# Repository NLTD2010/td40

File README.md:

# TD40

> **TD40** is a compact 40% mechanical keyboard designed for efficiency and portability.  
> It features **hot-swappable switches**, a **rotary knob**, an **OLED display**, **wireless connectivity**, and **per-key RGB lighting**.

---

## 🖼️ Preview

| TD40 (Back) | PCB |
|-------------|-----|
|  |  |

---

## ✨ Features
- Clean PCB design with **SMD soldering**
- **Nice!Nano v2** microcontroller – USB-C & Bluetooth compatible
- **Rotary encoder** + knob
- **0.91" OLED** screen
- **Per-key RGB** lighting
- **Hot-swappable** switches
- Open & visible components (Plaid / Romac style)
- Simple, flexible case options

---

## ⌨️ Layout

---

## 📦 Bill of Materials

| # | Item                         | Qty |
|---|------------------------------|----:|
| 1 | PCB                          | 1 |
| 2 | FR4 plate                    | 1 |
| 3 | Mica case                    | 1 |
| 4 | Controller (**Nice!Nano v2**) | 1 |
| 5 | Switches (5-pin MX footprint)| 45 |
| 6 | Kailh hotswap socket         | 45 |
| 7 | Diodes                       | 46 |
| 8 | Rotary encoder & knob        | 1 |
| 9 | 0.91" OLED screen            | 1 |

---

💡 **Tip:** Check out the [repository](https://github.com/NLTD2010/td40) for firmware, build guide, and more!

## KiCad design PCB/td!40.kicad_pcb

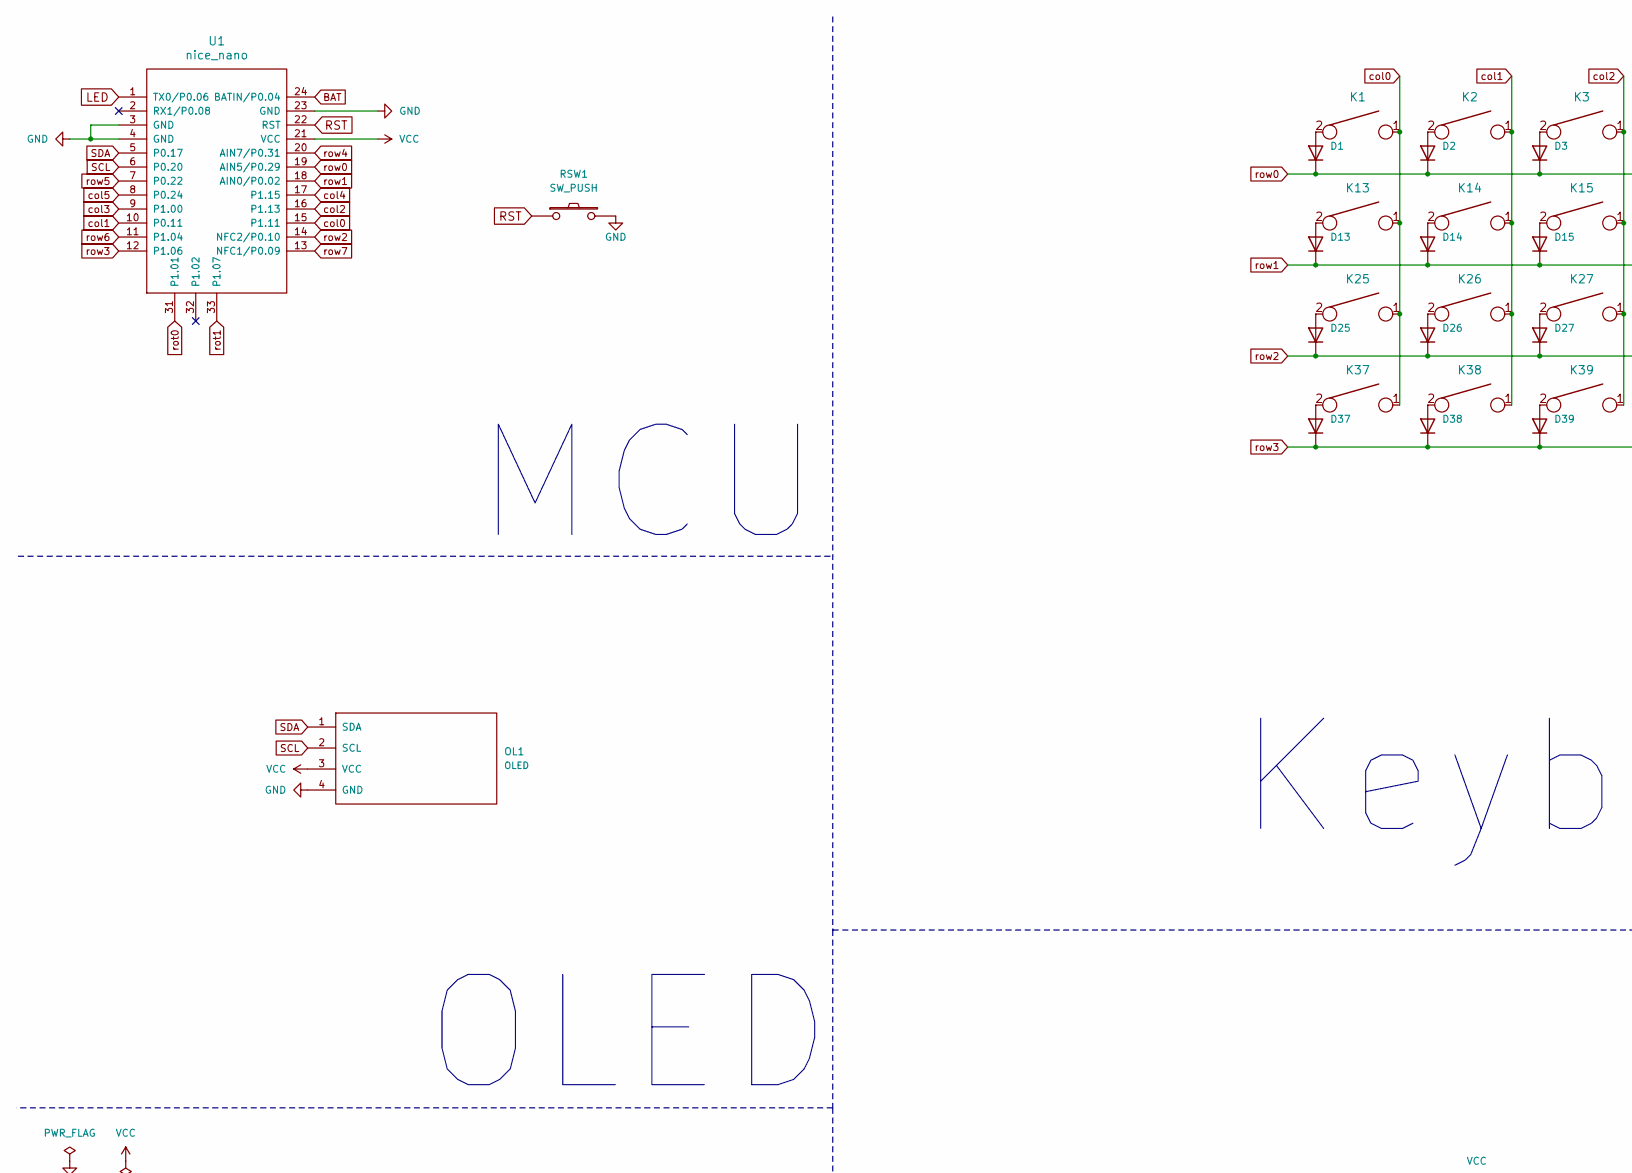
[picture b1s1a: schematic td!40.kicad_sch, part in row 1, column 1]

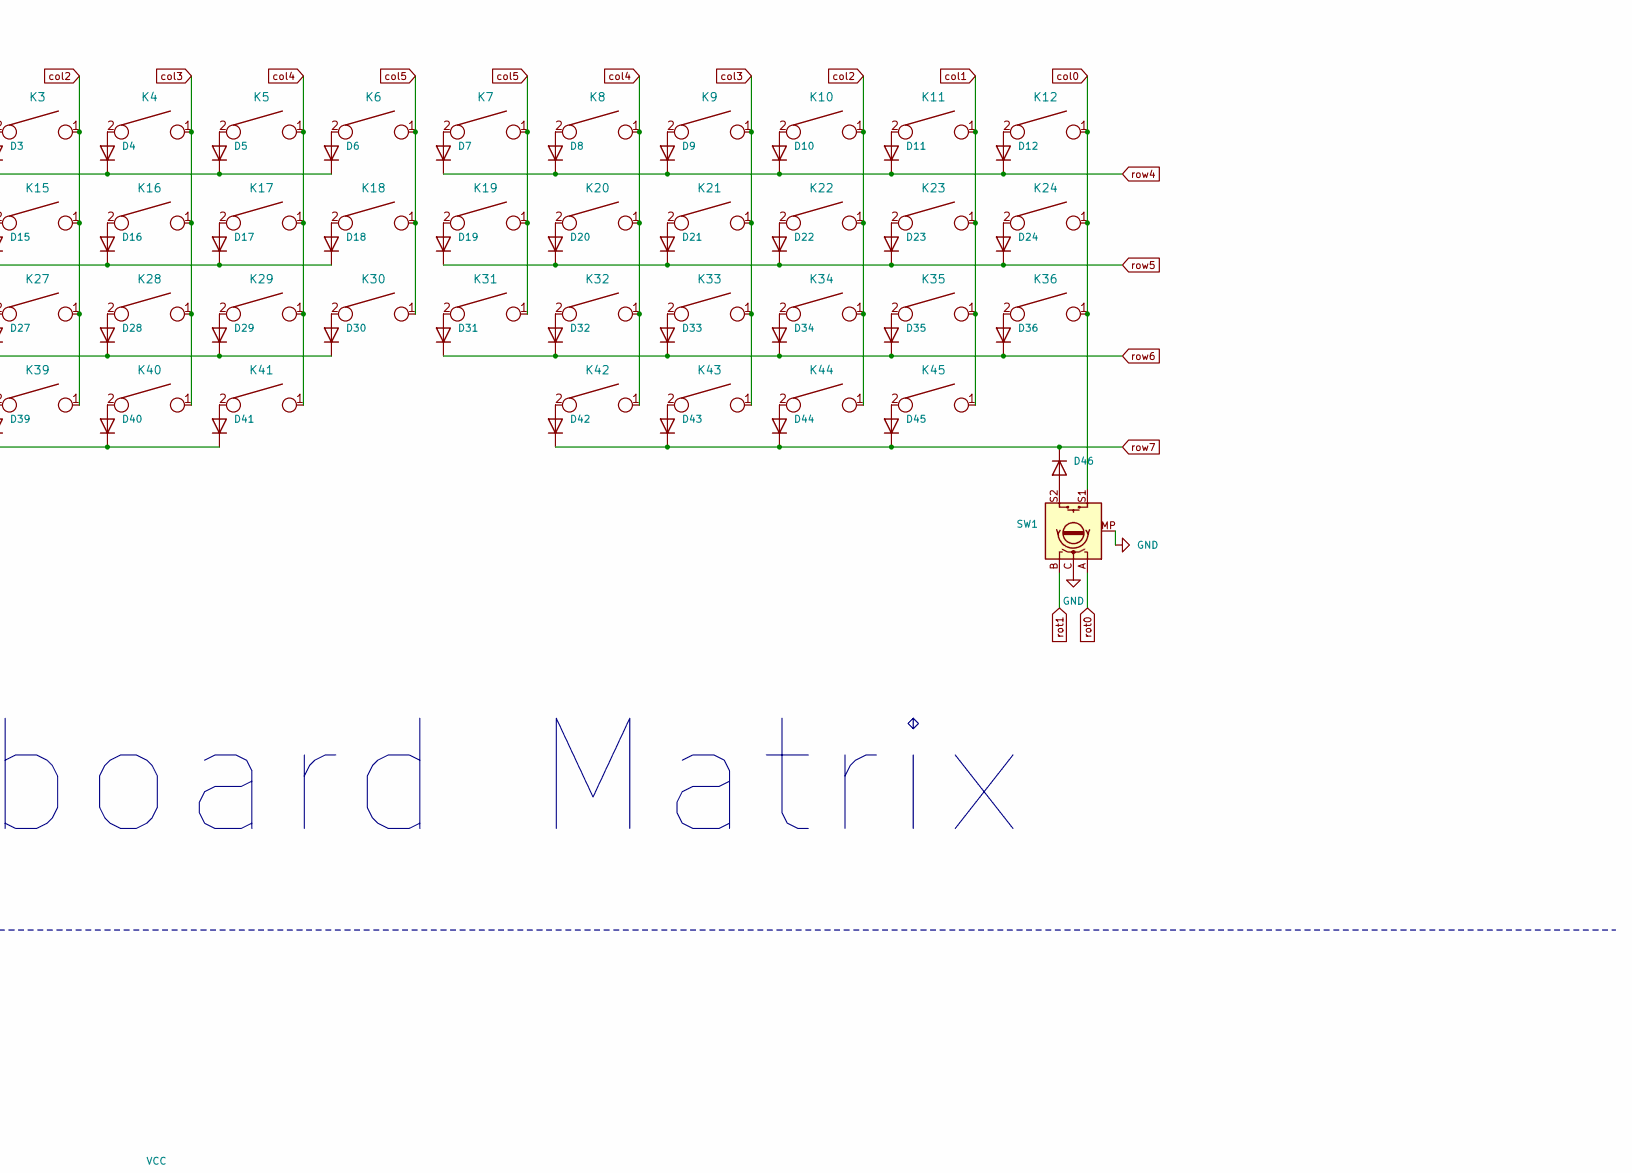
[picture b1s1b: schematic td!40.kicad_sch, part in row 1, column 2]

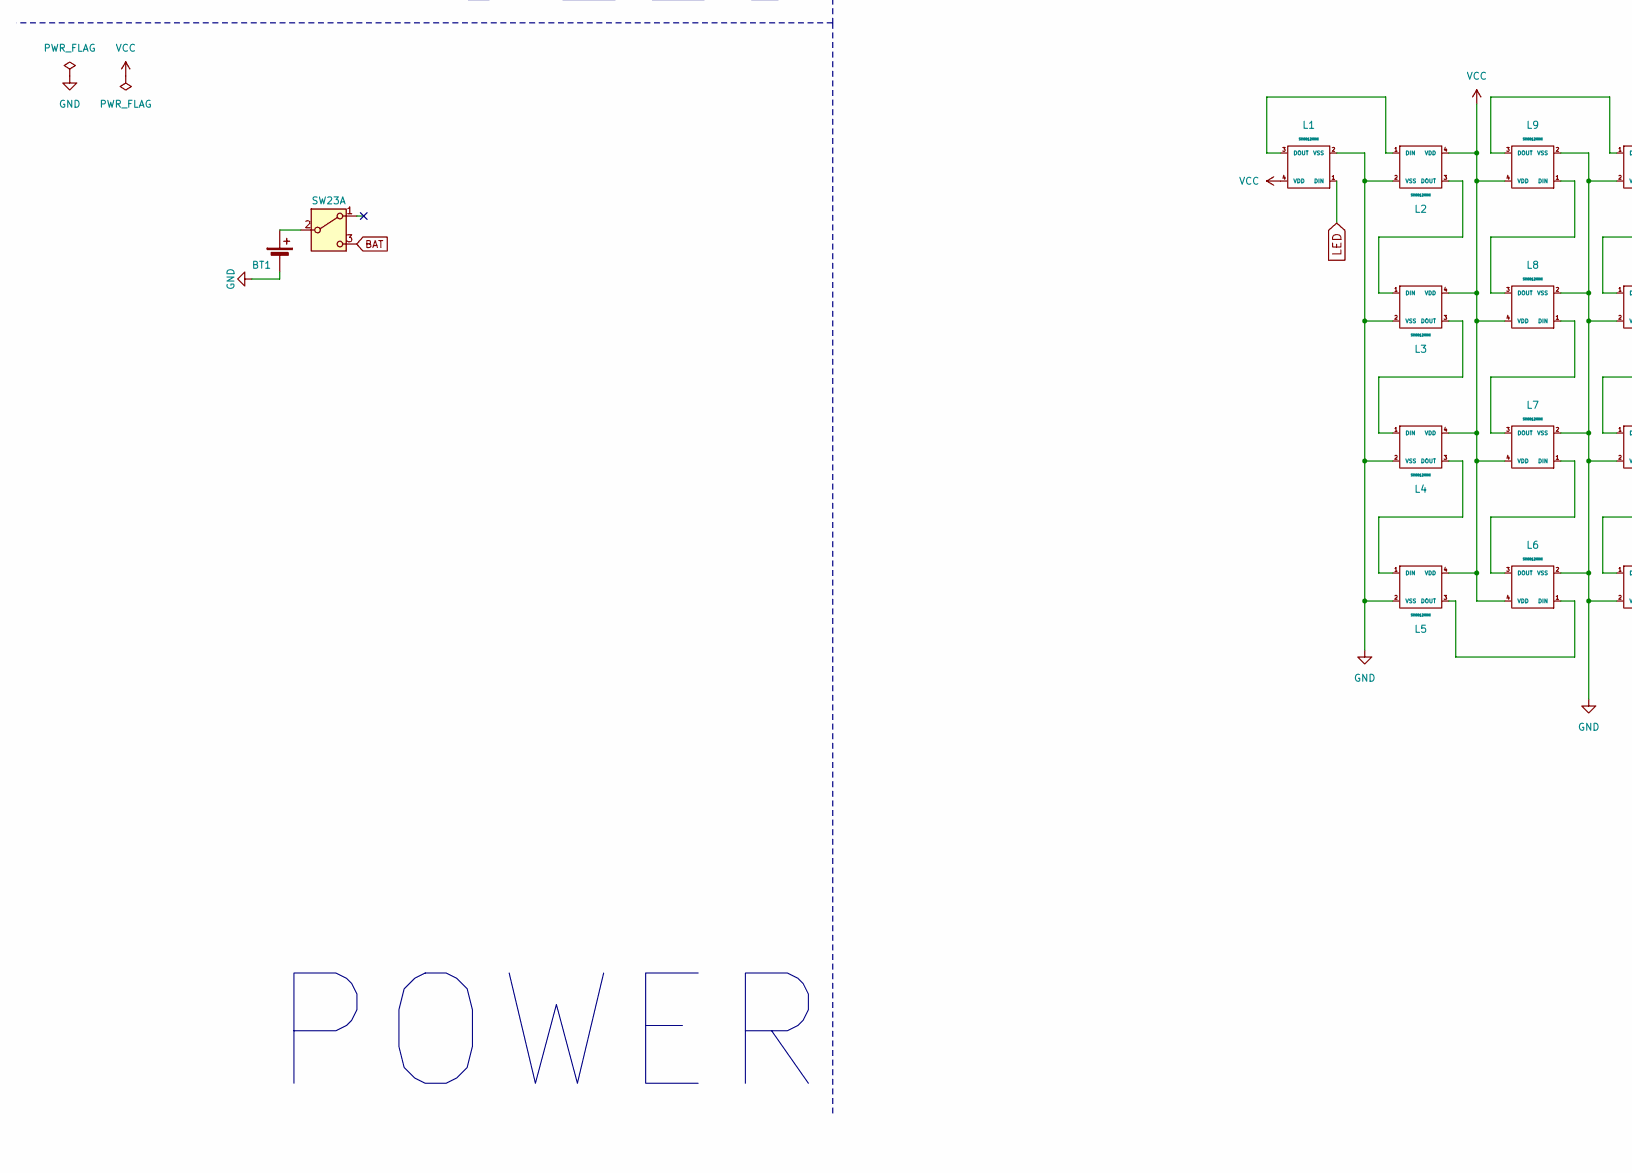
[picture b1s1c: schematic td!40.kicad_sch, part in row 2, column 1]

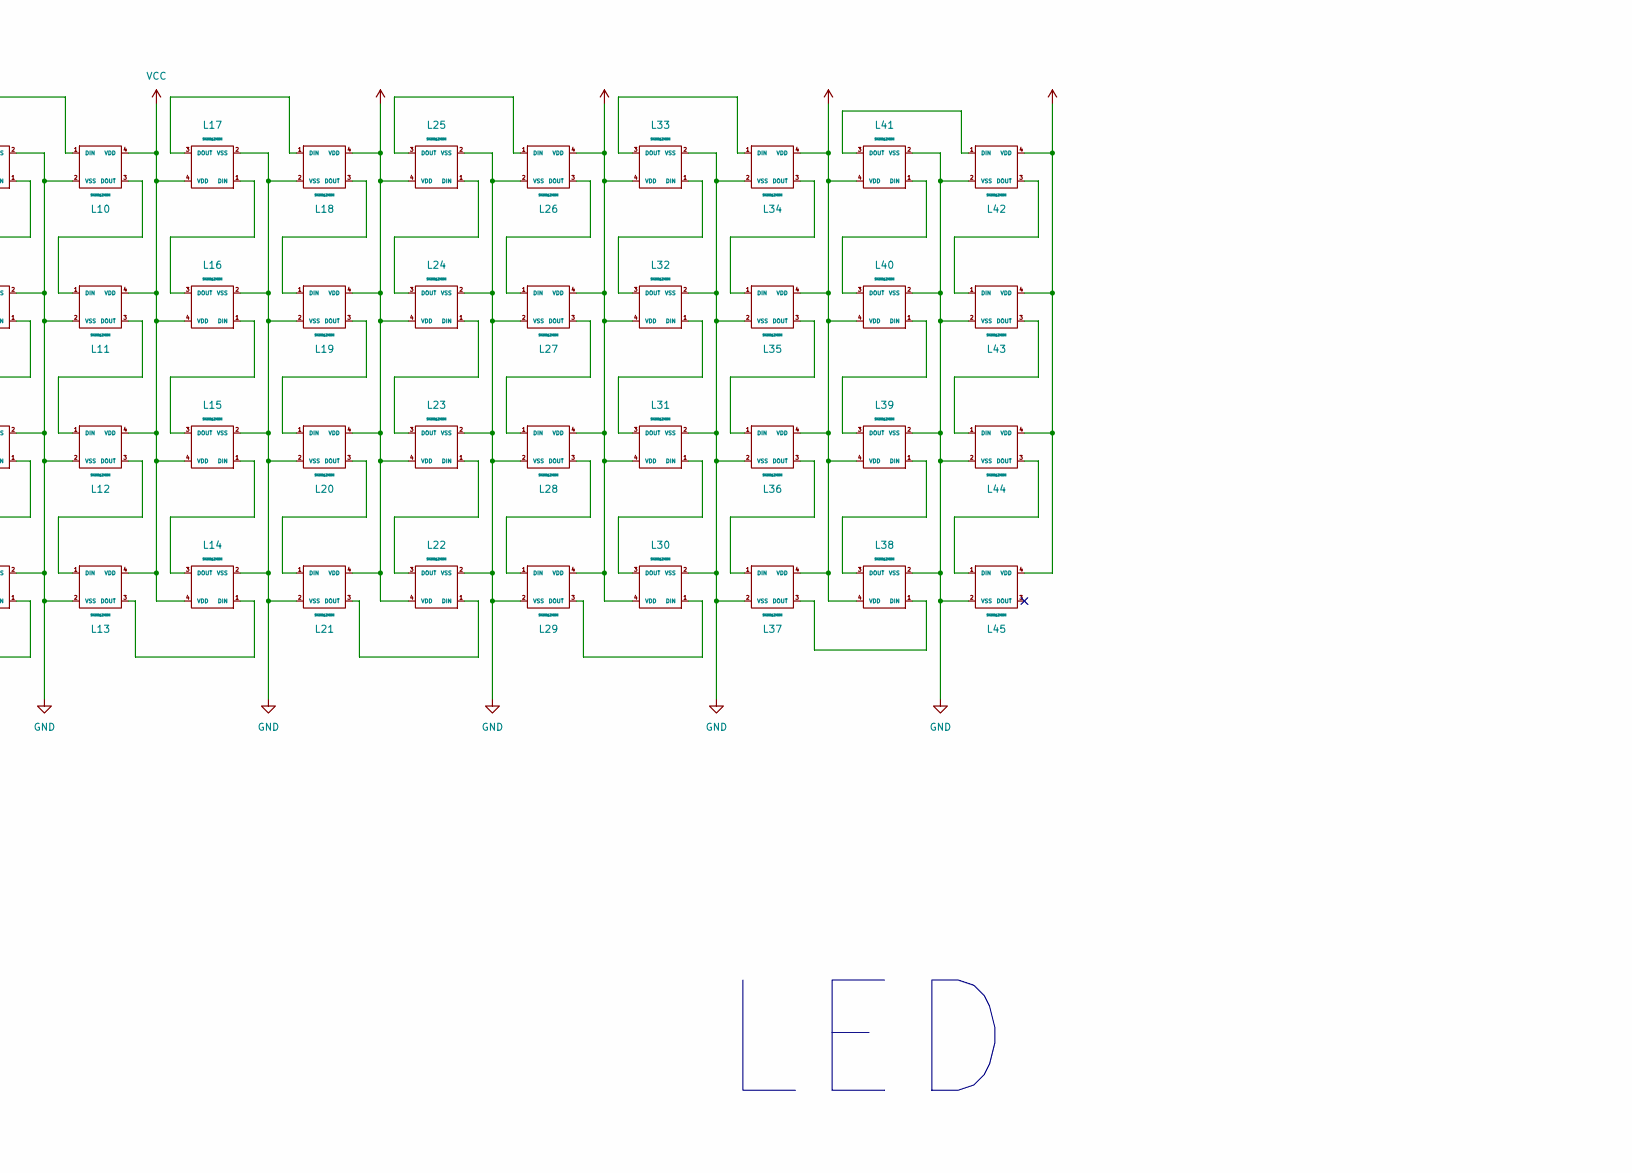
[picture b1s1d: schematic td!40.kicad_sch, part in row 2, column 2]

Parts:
BT1: Battery_Cell; JST_PH_S2B-PH-K_1x02_P2.00mm_Horizontal_flipped
D1, D2, D3, D4, D5, D6, D7, D8, D9, D10, D11, D12, D13, D14, D15, D16, D17, D18, D19, D20, D21, D22, D23, D24, D25, D26, D27, D28, D29, D30, D31, D32, D33, D34, D35, D36, D37, D38, D39, D40, D41, D42, D43, D44, D45: D_SOD-123
D46: D; D_SOD-123
K1, K2, K3, K4, K5, K6, K7, K8, K9, K10, K11, K14, K15, K16, K17, K18, K19, K20, K21, K22, K23, K26, K27, K28, K29, K30, K31, K32, K33, K34, K35, K36, K42, K43, K44, K45: KEYSW; MX-Hotswap-1U
K12, K25: KEYSW; MX-Hotswap-1.75U
K13, K37, K38, K39: KEYSW; MX-Hotswap-1.25U
K24: KEYSW; MX-Hotswap-1.5U
K40: KEYSW; MX-Hotswap-2.25U-ReversedStabilizers
K41: KEYSW; MX-Hotswap-2.75U-ReversedStabilizers
L1, L2, L3, L4, L5, L6, L7, L8, L9, L10, L11, L12, L13, L14, L15, L16, L17, L18, L19, L20, L21, L22, L23, L24, L25, L26, L27, L28, L29, L30, L31, L32, L33, L34, L35, L36, L37, L38, L39, L40, L41, L42, L43, L44, L45: SK6812MINI; YS-SK6812MINI-E
OL1: OLED
RSW1: SW_PUSH; ResetSW
SW1: RotaryEncoder_Switch; RotaryEncoder_Alps_EC11E-Switch_Vertical_H20mm
SW23: SW23; switch-MSK-12C02-smd
U1: nice_nano

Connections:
BAT: SW23.3 (C), U1.24 (BATIN/P0.04)
GND: BT1.2 (-), L1.2 (VSS), L2.2 (VSS), L3.2 (VSS), L4.2 (VSS), L5.2 (VSS), L6.2 (VSS), L7.2 (VSS), L8.2 (VSS), L9.2 (VSS), L10.2 (VSS), L11.2 (VSS), L12.2 (VSS), L13.2 (VSS), L14.2 (VSS), L15.2 (VSS), L16.2 (VSS), L17.2 (VSS), L18.2 (VSS), L19.2 (VSS), L20.2 (VSS), L21.2 (VSS), L22.2 (VSS), L23.2 (VSS), L24.2 (VSS), L25.2 (VSS), L26.2 (VSS), L27.2 (VSS), L28.2 (VSS), L29.2 (VSS), L30.2 (VSS), L31.2 (VSS), L32.2 (VSS), L33.2 (VSS), L34.2 (VSS), L35.2 (VSS), L36.2 (VSS), L37.2 (VSS), L38.2 (VSS), L39.2 (VSS), L40.2 (VSS), L41.2 (VSS), L42.2 (VSS), L43.2 (VSS), L44.2 (VSS), L45.2 (VSS), OL1.4 (GND), RSW1.2, SW1.C, SW1.MP, U1.3 (GND), U1.4 (GND), U1.23 (GND)
LED: L1.1 (DIN), U1.1 (TX0/P0.06)
unnamed: BT1.1 (+), SW23.2 (B)
unnamed: D1.2 (A), K1.2
unnamed: D2.2 (A), K2.2
unnamed: D3.2 (A), K3.2
unnamed: D4.2 (A), K4.2
unnamed: D5.2 (A), K5.2
unnamed: D6.2 (A), K6.2
unnamed: D7.2 (A), K7.2
unnamed: D8.2 (A), K8.2
unnamed: D9.2 (A), K9.2
unnamed: D10.2 (A), K10.2
unnamed: D11.2 (A), K11.2
unnamed: D12.2 (A), K12.2
unnamed: D13.2 (A), K13.2
unnamed: D14.2 (A), K14.2
unnamed: D15.2 (A), K15.2
unnamed: D16.2 (A), K16.2
unnamed: D17.2 (A), K17.2
unnamed: D18.2 (A), K18.2
unnamed: D19.2 (A), K19.2
unnamed: D20.2 (A), K20.2
unnamed: D21.2 (A), K21.2
unnamed: D22.2 (A), K22.2
unnamed: D23.2 (A), K23.2
unnamed: D24.2 (A), K24.2
unnamed: D25.2 (A), K25.2
unnamed: D26.2 (A), K26.2
unnamed: D27.2 (A), K27.2
unnamed: D28.2 (A), K28.2
unnamed: D29.2 (A), K29.2
unnamed: D30.2 (A), K30.2
unnamed: D31.2 (A), K31.2
unnamed: D32.2 (A), K32.2
unnamed: D33.2 (A), K33.2
unnamed: D34.2 (A), K34.2
unnamed: D35.2 (A), K35.2
unnamed: D36.2 (A), K36.2
unnamed: D37.2 (A), K37.2
unnamed: D38.2 (A), K38.2
unnamed: D39.2 (A), K39.2
unnamed: D40.2 (A), K40.2
unnamed: D41.2 (A), K41.2
unnamed: D42.2 (A), K42.2
unnamed: D43.2 (A), K43.2
unnamed: D44.2 (A), K44.2
unnamed: D45.2 (A), K45.2
unnamed: D46.2 (A), SW1.S2
unnamed: L1.3 (DOUT), L2.1 (DIN)
unnamed: L2.3 (DOUT), L3.1 (DIN)
unnamed: L3.3 (DOUT), L4.1 (DIN)
unnamed: L4.3 (DOUT), L5.1 (DIN)
unnamed: L5.3 (DOUT), L6.1 (DIN)
unnamed: L6.3 (DOUT), L7.1 (DIN)
unnamed: L7.3 (DOUT), L8.1 (DIN)
unnamed: L8.3 (DOUT), L9.1 (DIN)
unnamed: L9.3 (DOUT), L10.1 (DIN)
unnamed: L10.3 (DOUT), L11.1 (DIN)
unnamed: L11.3 (DOUT), L12.1 (DIN)
unnamed: L12.3 (DOUT), L13.1 (DIN)
unnamed: L13.3 (DOUT), L14.1 (DIN)
unnamed: L14.3 (DOUT), L15.1 (DIN)
unnamed: L15.3 (DOUT), L16.1 (DIN)
unnamed: L16.3 (DOUT), L17.1 (DIN)
unnamed: L17.3 (DOUT), L18.1 (DIN)
unnamed: L18.3 (DOUT), L19.1 (DIN)
unnamed: L19.3 (DOUT), L20.1 (DIN)
unnamed: L20.3 (DOUT), L21.1 (DIN)
unnamed: L21.3 (DOUT), L22.1 (DIN)
unnamed: L22.3 (DOUT), L23.1 (DIN)
unnamed: L23.3 (DOUT), L24.1 (DIN)
unnamed: L24.3 (DOUT), L25.1 (DIN)
unnamed: L25.3 (DOUT), L26.1 (DIN)
unnamed: L26.3 (DOUT), L27.1 (DIN)
unnamed: L27.3 (DOUT), L28.1 (DIN)
unnamed: L28.3 (DOUT), L29.1 (DIN)
unnamed: L29.3 (DOUT), L30.1 (DIN)
unnamed: L30.3 (DOUT), L31.1 (DIN)
unnamed: L31.3 (DOUT), L32.1 (DIN)
unnamed: L32.3 (DOUT), L33.1 (DIN)
unnamed: L33.3 (DOUT), L34.1 (DIN)
unnamed: L34.3 (DOUT), L35.1 (DIN)
unnamed: L35.3 (DOUT), L36.1 (DIN)
unnamed: L36.3 (DOUT), L37.1 (DIN)
unnamed: L37.3 (DOUT), L38.1 (DIN)
unnamed: L38.3 (DOUT), L39.1 (DIN)
unnamed: L39.3 (DOUT), L40.1 (DIN)
unnamed: L40.3 (DOUT), L41.1 (DIN)
unnamed: L41.3 (DOUT), L42.1 (DIN)
unnamed: L42.3 (DOUT), L43.1 (DIN)
unnamed: L43.3 (DOUT), L44.1 (DIN)
unnamed: L44.3 (DOUT), L45.1 (DIN)
RST: RSW1.1, U1.22 (RST)
SCL: OL1.2 (SCL), U1.6 (P0.20)
SDA: OL1.1 (SDA), U1.5 (P0.17)
VCC: L1.4 (VDD), L2.4 (VDD), L3.4 (VDD), L4.4 (VDD), L5.4 (VDD), L6.4 (VDD), L7.4 (VDD), L8.4 (VDD), L9.4 (VDD), L10.4 (VDD), L11.4 (VDD), L12.4 (VDD), L13.4 (VDD), L14.4 (VDD), L15.4 (VDD), L16.4 (VDD), L17.4 (VDD), L18.4 (VDD), L19.4 (VDD), L20.4 (VDD), L21.4 (VDD), L22.4 (VDD), L23.4 (VDD), L24.4 (VDD), L25.4 (VDD), L26.4 (VDD), L27.4 (VDD), L28.4 (VDD), L29.4 (VDD), L30.4 (VDD), L31.4 (VDD), L32.4 (VDD), L33.4 (VDD), L34.4 (VDD), L35.4 (VDD), L36.4 (VDD), L37.4 (VDD), L38.4 (VDD), L39.4 (VDD), L40.4 (VDD), L41.4 (VDD), L42.4 (VDD), L43.4 (VDD), L44.4 (VDD), L45.4 (VDD), OL1.3 (VCC), U1.21 (VCC)
col0: K1.1, K12.1, K13.1, K24.1, K25.1, K36.1, K37.1, SW1.S1, U1.15 (P1.11)
col1: K2.1, K11.1, K14.1, K23.1, K26.1, K35.1, K38.1, K45.1, U1.10 (P0.11)
col2: K3.1, K10.1, K15.1, K22.1, K27.1, K34.1, K39.1, K44.1, U1.16 (P1.13)
col3: K4.1, K9.1, K16.1, K21.1, K28.1, K33.1, K40.1, K43.1, U1.9 (P1.00)
col4: K5.1, K8.1, K17.1, K20.1, K29.1, K32.1, K41.1, K42.1, U1.17 (P1.15)
col5: K6.1, K7.1, K18.1, K19.1, K30.1, K31.1, U1.8 (P0.24)
rot0: SW1.A, U1.31 (P1.01)
rot1: SW1.B, U1.33 (P1.07)
row0: D1.1 (K), D2.1 (K), D3.1 (K), D4.1 (K), D5.1 (K), D6.1 (K), U1.19 (AIN5/P0.29)
row1: D13.1 (K), D14.1 (K), D15.1 (K), D16.1 (K), D17.1 (K), D18.1 (K), U1.18 (AIN0/P0.02)
row2: D25.1 (K), D26.1 (K), D27.1 (K), D28.1 (K), D29.1 (K), D30.1 (K), U1.14 (NFC2/P0.10)
row3: D37.1 (K), D38.1 (K), D39.1 (K), D40.1 (K), D41.1 (K), U1.12 (P1.06)
row4: D7.1 (K), D8.1 (K), D9.1 (K), D10.1 (K), D11.1 (K), D12.1 (K), U1.20 (AIN7/P0.31)
row5: D19.1 (K), D20.1 (K), D21.1 (K), D22.1 (K), D23.1 (K), D24.1 (K), U1.7 (P0.22)
row6: D31.1 (K), D32.1 (K), D33.1 (K), D34.1 (K), D35.1 (K), D36.1 (K), U1.11 (P1.04)
row7: D42.1 (K), D43.1 (K), D44.1 (K), D45.1 (K), D46.1 (K), U1.13 (NFC1/P0.09)

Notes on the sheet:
LED
MCU
OLED
POWER
Keyboard Matrix

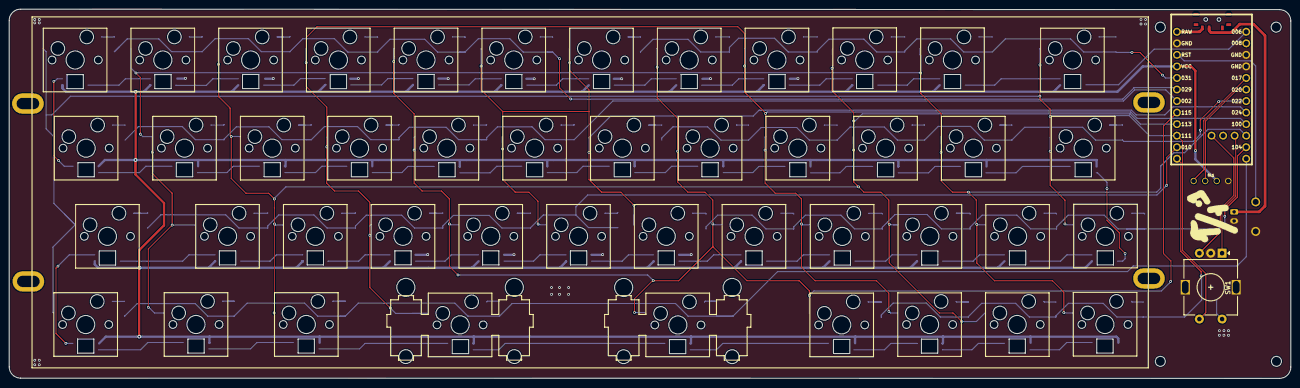
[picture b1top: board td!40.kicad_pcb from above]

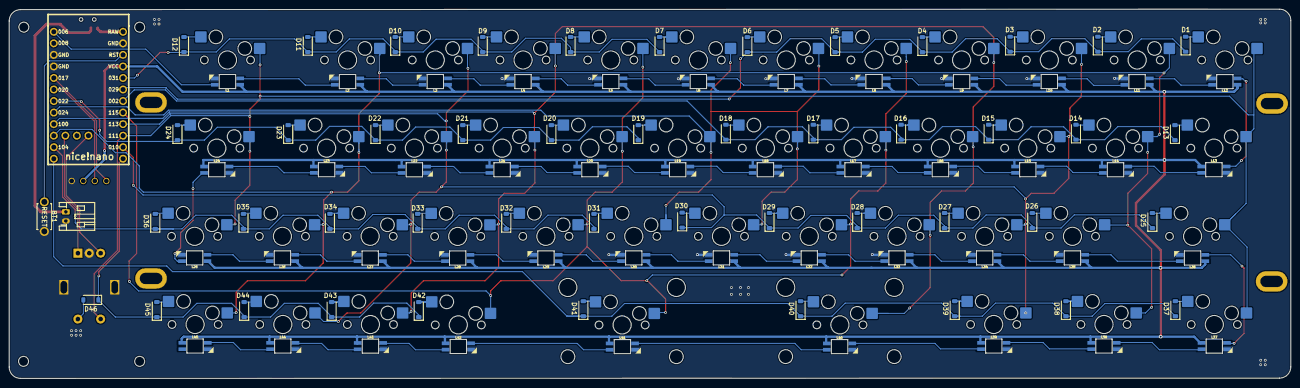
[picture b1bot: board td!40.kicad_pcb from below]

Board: 2 copper layers, 282.1 x 81.3 mm, 146 parts (139 on the bottom side), 114 nets.

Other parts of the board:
M1, M2, M3, M4: MountingHole_2.2mm_M2

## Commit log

2025-08-16 Add schematic and KLE layout
2025-08-17 PCB finished
2025-08-29 Update: No more DRC errors, yayy
2025-09-04 Add ZMK firmware
2025-09-04 Fix Github Actions
2025-09-05 Try to make the oled working
2025-09-06 Try to fix the bluetooth and add ZMK studio support
2025-09-13 Fix display
2025-09-18 Correct the RGB SK6812 pinout
2025-09-18 Add README.md, 3D models and images
2025-09-18 Update README.md :D
2025-09-19 Update Github Actions for create release
